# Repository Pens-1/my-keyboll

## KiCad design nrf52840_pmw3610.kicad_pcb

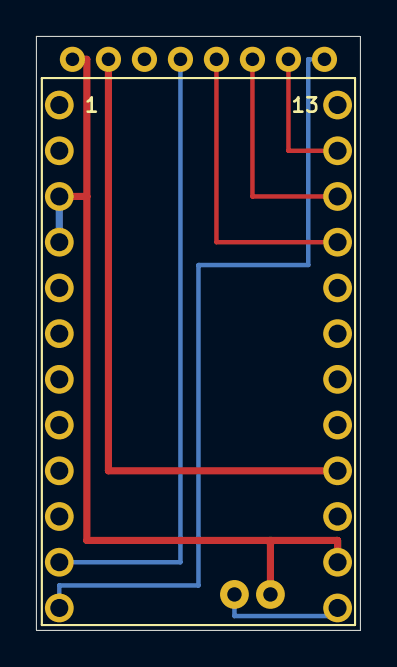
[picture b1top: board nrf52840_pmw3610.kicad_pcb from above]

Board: 2 copper layers, 18.0 x 33.0 mm, 3 parts (0 on the bottom side), 8 nets.

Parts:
J1: PMW3360_Connector; Connector_JST_PH_1x08
J2: Battery_JST-PH; Connector_JST_PH_2pin
U1: SuperMini_nRF52840; SuperMini_nRF52840_Socket

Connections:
BATIN: J2.1, U1.24
GND: J1.1, J2.2, U1.3, U1.4, U1.23
MISO: J1.7, U1.14
MOSI: J1.6, U1.15
MOTION: J1.4, U1.11
NCS: J1.8, U1.12
SCK: J1.5, U1.16
VCC: J1.2, U1.21

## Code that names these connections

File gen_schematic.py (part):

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  MOSI  : SuperMini pin14 (P0.10)  → PMW3610 pin6
  MISO  : SuperMini pin15 (P1.11)  → PMW3610 pin7
  SCK   : SuperMini pin16 (P1.13)  → PMW3610 pin5
  NCS   : SuperMini pin12 (P1.06)  → PMW3610 pin8
  MOTION: SuperMini pin11 (P1.04)  → PMW3610 pin4

Battery connections:
  B+    : J2 pin1  → SuperMini pin24 (BATIN/P0.04) via BATIN net
  B-    : J2 pin2  → GND
"""

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    (comment 1 "SuperMini nRF52840 (nice!nano v2 compatible)")
    (comment 2 "PMW3610 (3.3V direct operation, no LDO required)")
    (comment 3 "SPI: MOSI=P0.10  MISO=P1.11  SCK=P1.13  NCS=P1.06")
    (comment 4 "MOTION=P1.04  VCC=3.3V from SuperMini pin21  BAT+=BATIN/P0.04")
  )
""")

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    parts.append(wire(sx_j1 - SPI_LABEL_LEN, sy_j1, sx_j1, sy_j1))
    parts.append(net_label("SCK", sx_j1 - SPI_LABEL_LEN, sy_j1, 180))

    # --- NCS: U1 pin12 (left) → label → J1 pin8 ---
    ncx_u1, ncy_u1 = u1_left_abs(12)
    parts.append(wire(ncx_u1 - SPI_LABEL_LEN, ncy_u1, ncx_u1, ncy_u1))
    parts.append(net_label("NCS", ncx_u1 - SPI_LABEL_LEN, ncy_u1, 180))

    ncx_j1, ncy_j1 = j1_left_abs(8)
    parts.append(wire(ncx_j1 - SPI_LABEL_LEN, ncy_j1, ncx_j1, ncy_j1))
    parts.append(net_label("NCS", ncx_j1 - SPI_LABEL_LEN, ncy_j1, 180))

    # --- MOTION: U1 pin11 (left) → label → J1 pin4 ---
    motx_u1, moty_u1 = u1_left_abs(11)
    parts.append(wire(motx_u1 - SPI_LABEL_LEN, moty_u1, motx_u1, moty_u1))
    parts.append(net_label("MOTION", motx_u1 - SPI_LABEL_LEN, moty_u1, 180))

    motx_j1, moty_j1 = j1_left_abs(4)
    parts.append(wire(motx_j1 - SPI_LABEL_LEN, moty_j1, motx_j1, moty_j1))
    parts.append(net_label("MOTION", motx_j1 - SPI_LABEL_LEN, moty_j1, 180))

    # ── Battery connector J2 ─────────────────────────────────────────────────
    BATT_LABEL_LEN = 5.08

    # J2 pin1 B+ → net label BATIN
    bp_x, bp_y = j2_left_abs(1)
    parts.append(wire(bp_x - BATT_LABEL_LEN, bp_y, bp_x, bp_y))
    parts.append(net_label("BATIN", bp_x - BATT_LABEL_LEN, bp_y, 180))

    # J2 pin2 B- → GND
    bm_x, bm_y = j2_left_abs(2)
    parts.append(power_sym(bm_x - 2.54, bm_y, "GND", "#PWR07"))
    parts.append(wire(bm_x - 2.54, bm_y, bm_x, bm_y))

    # U1 pin24 BATIN/P0.04 (right side) → net label BATIN
    bat_u1x, bat_u1y = u1_right_abs(24)
    parts.append(wire(bat_u1x, bat_u1y, bat_u1x + BATT_LABEL_LEN, bat_u1y))
    parts.append(net_label("BATIN", bat_u1x + BATT_LABEL_LEN, bat_u1y, 0))

    # ── No-connects for unused pins ──────────────────────────────────────────
    unused_left  = [1, 2, 5, 6, 7, 8, 9, 10]   # U1 left
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
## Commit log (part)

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2026-03-20 feat: nRF52840 + PMW3360回路図追加
2026-03-20 feat: J2バッテリーコネクタ追加（B+→BATIN/P0.04、B-→GND）
2026-03-20 feat: Pro Microフットプリント(18x33mm)PCBレイアウト生成
2026-03-20 fix: KiCad 9.0対応 F.CrtYdレイヤー番号修正・stroke形式対応
2026-03-21 add:DRC.rptを追加
2026-03-25 fix: BATINルートをy=30.5に変更してU1R pin23(GND)パッドとの短絡を解消
2026-03-25 fix: BATINルートをJ2 pad2下側(y=32.2)経由に変更して短絡を解消
2026-03-25 add: Keyball39カスタム回路図（22キーマトリクス+PMW3610+SuperMini）
